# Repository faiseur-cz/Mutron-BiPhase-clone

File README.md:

# Mutron-BiPhase-clone
DIY clone of the famous phaser

I started a thread at modwiggler, feel free to participate over there :
https://www.modwiggler.com/forum/viewtopic.php?t=290870

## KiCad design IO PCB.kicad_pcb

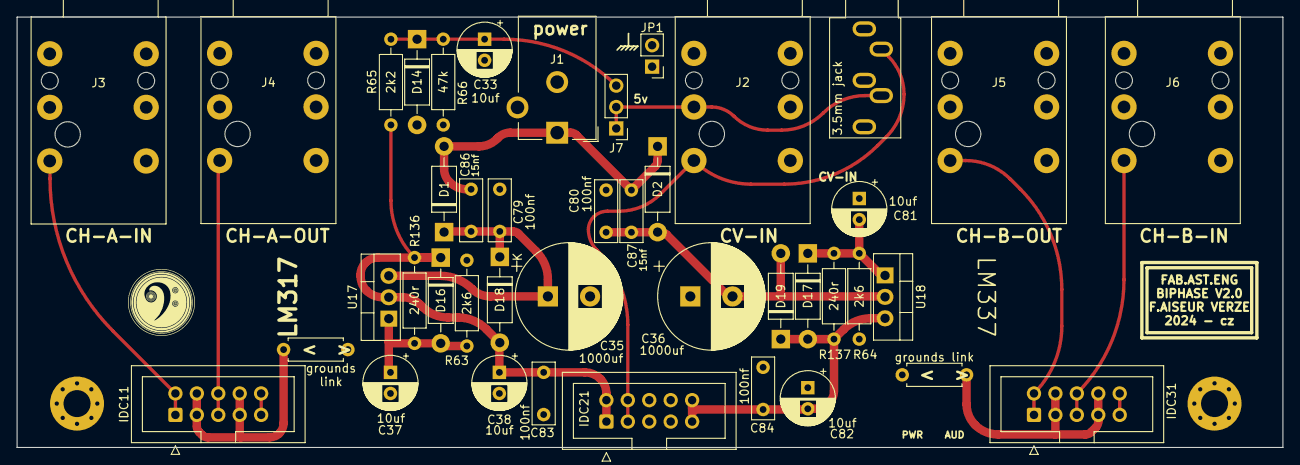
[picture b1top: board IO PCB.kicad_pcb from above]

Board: 2 copper layers, 150.0 x 51.0 mm, 44 parts (0 on the bottom side), 18 nets.

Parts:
C33, C37, C38, C81, C82: 10uf; CP_Radial_D6.3mm_P2.50mm
C35, C36: 1000uf; CP_Radial_D12.5mm_P5.00mm
C79, C80, C83, C84: 100nf; C_Rect_L7.2mm_W2.5mm_P5.00mm_FKS2_FKP2_MKS2_MKP2
C86, C87: 15nf; C_Rect_L7.2mm_W2.5mm_P5.00mm_FKS2_FKP2_MKS2_MKP2
D1, D2, D16, D17, D18, D19: 1N4004; D_DO-41_SOD81_P10.16mm_Horizontal
D14: 5V1; D_DO-41_SOD81_P10.16mm_Horizontal
H2, H8: MountingHole_Pad; MountingHole_3.2mm_M3_Pad_Via
IDC11, IDC21, IDC31: Conn_02x05_Odd_Even; IDC-Header_2x05_P2.54mm_Vertical
J1: Barrel_Jack_Switch; BarrelJack_CUI_PJ-102AH_Horizontal
J2, J3, J4, J5, J6: NRJ6HF; Jack_6.35mm_Neutrik_NRJ6HF_Horizontal
J7: Conn_01x03; PinHeader_1x03_P2.54mm_Vertical
J8: 3.5mm jack; Jack_3.5mm_CUI_SJ1-3535NG_Horizontal
JP1: Jumper_2_Open; PinHeader_1x02_P2.54mm_Vertical
JP2, JP3: grounds link; R_Axial_DIN0207_L6.3mm_D2.5mm_P7.62mm_Horizontal
R63, R64: 2k6; R_Axial_DIN0207_L6.3mm_D2.5mm_P10.16mm_Horizontal
R65: 2k2; R_Axial_DIN0207_L6.3mm_D2.5mm_P10.16mm_Horizontal
R66: 47k; R_Axial_DIN0207_L6.3mm_D2.5mm_P10.16mm_Horizontal
R136, R137: 240r; R_Axial_DIN0207_L6.3mm_D2.5mm_P10.16mm_Horizontal
U17: LM317; TO-220-3_Vertical
U18: LM337; TO-220-3_Vertical

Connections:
5v: C33.1, D14.1 (K), J7.3, R65.1, R66.1
GND: IDC11.3, IDC11.4, IDC11.7, IDC11.8, IDC31.3, IDC31.4, IDC31.7, IDC31.8, J3.S, J3.SN, J3.TN, J4.S, J4.SN, J5.S, J5.SN, J5.TN, J6.S, J6.SN, JP2.1 (A), JP3.1 (A)
GND5: C33.2, C35.2, C36.1, C37.2, C38.2, C79.2, C80.1, C81.1, C82.1, C83.2, C84.1, D14.2 (A), H2.1, H8.1, IDC21.5, IDC21.6, IDC21.7, IDC21.8, J1.2, J2.S, J2.SN, J2.TN, J8.S, J8.TN, JP1.1 (A), JP1.2 (B), JP2.2 (B), JP3.2 (B), R63.2, R64.1, R66.2
unnamed: C86.2, C87.1, D1.2 (A), D2.1 (K), J1.1
unnamed: C35.1, C79.1, C86.1, D1.1 (K), D18.1 (K), U17.3 (VI)
unnamed: C37.1, D16.2 (A), R63.1, R136.2, U17.1 (ADJ)
unnamed: C38.1, C83.1, D16.1 (K), D18.2 (A), IDC21.1, IDC21.2, R65.2, R136.1, U17.2 (VO)
unnamed: C82.2, C84.2, D17.2 (A), D19.1 (K), IDC21.9, IDC21.10, R137.2, U18.3 (VO)
unnamed: C81.2, D17.1 (K), R64.2, R137.1, U18.1 (ADJ)
unnamed: C36.2, C80.2, C87.2, D2.2 (A), D19.2 (A), U18.2 (VI)
unnamed: IDC11.1, IDC11.2, J3.T
unnamed: IDC11.5, IDC11.6, J4.T
unnamed: IDC11.9, IDC11.10
unnamed: IDC21.3, IDC21.4, J2.T, J8.T
unnamed: IDC31.1, IDC31.2, J5.T
unnamed: IDC31.5, IDC31.6, J6.T
unnamed: IDC31.9, IDC31.10
unnamed: J2.R, J7.1, J7.2, J8.R
